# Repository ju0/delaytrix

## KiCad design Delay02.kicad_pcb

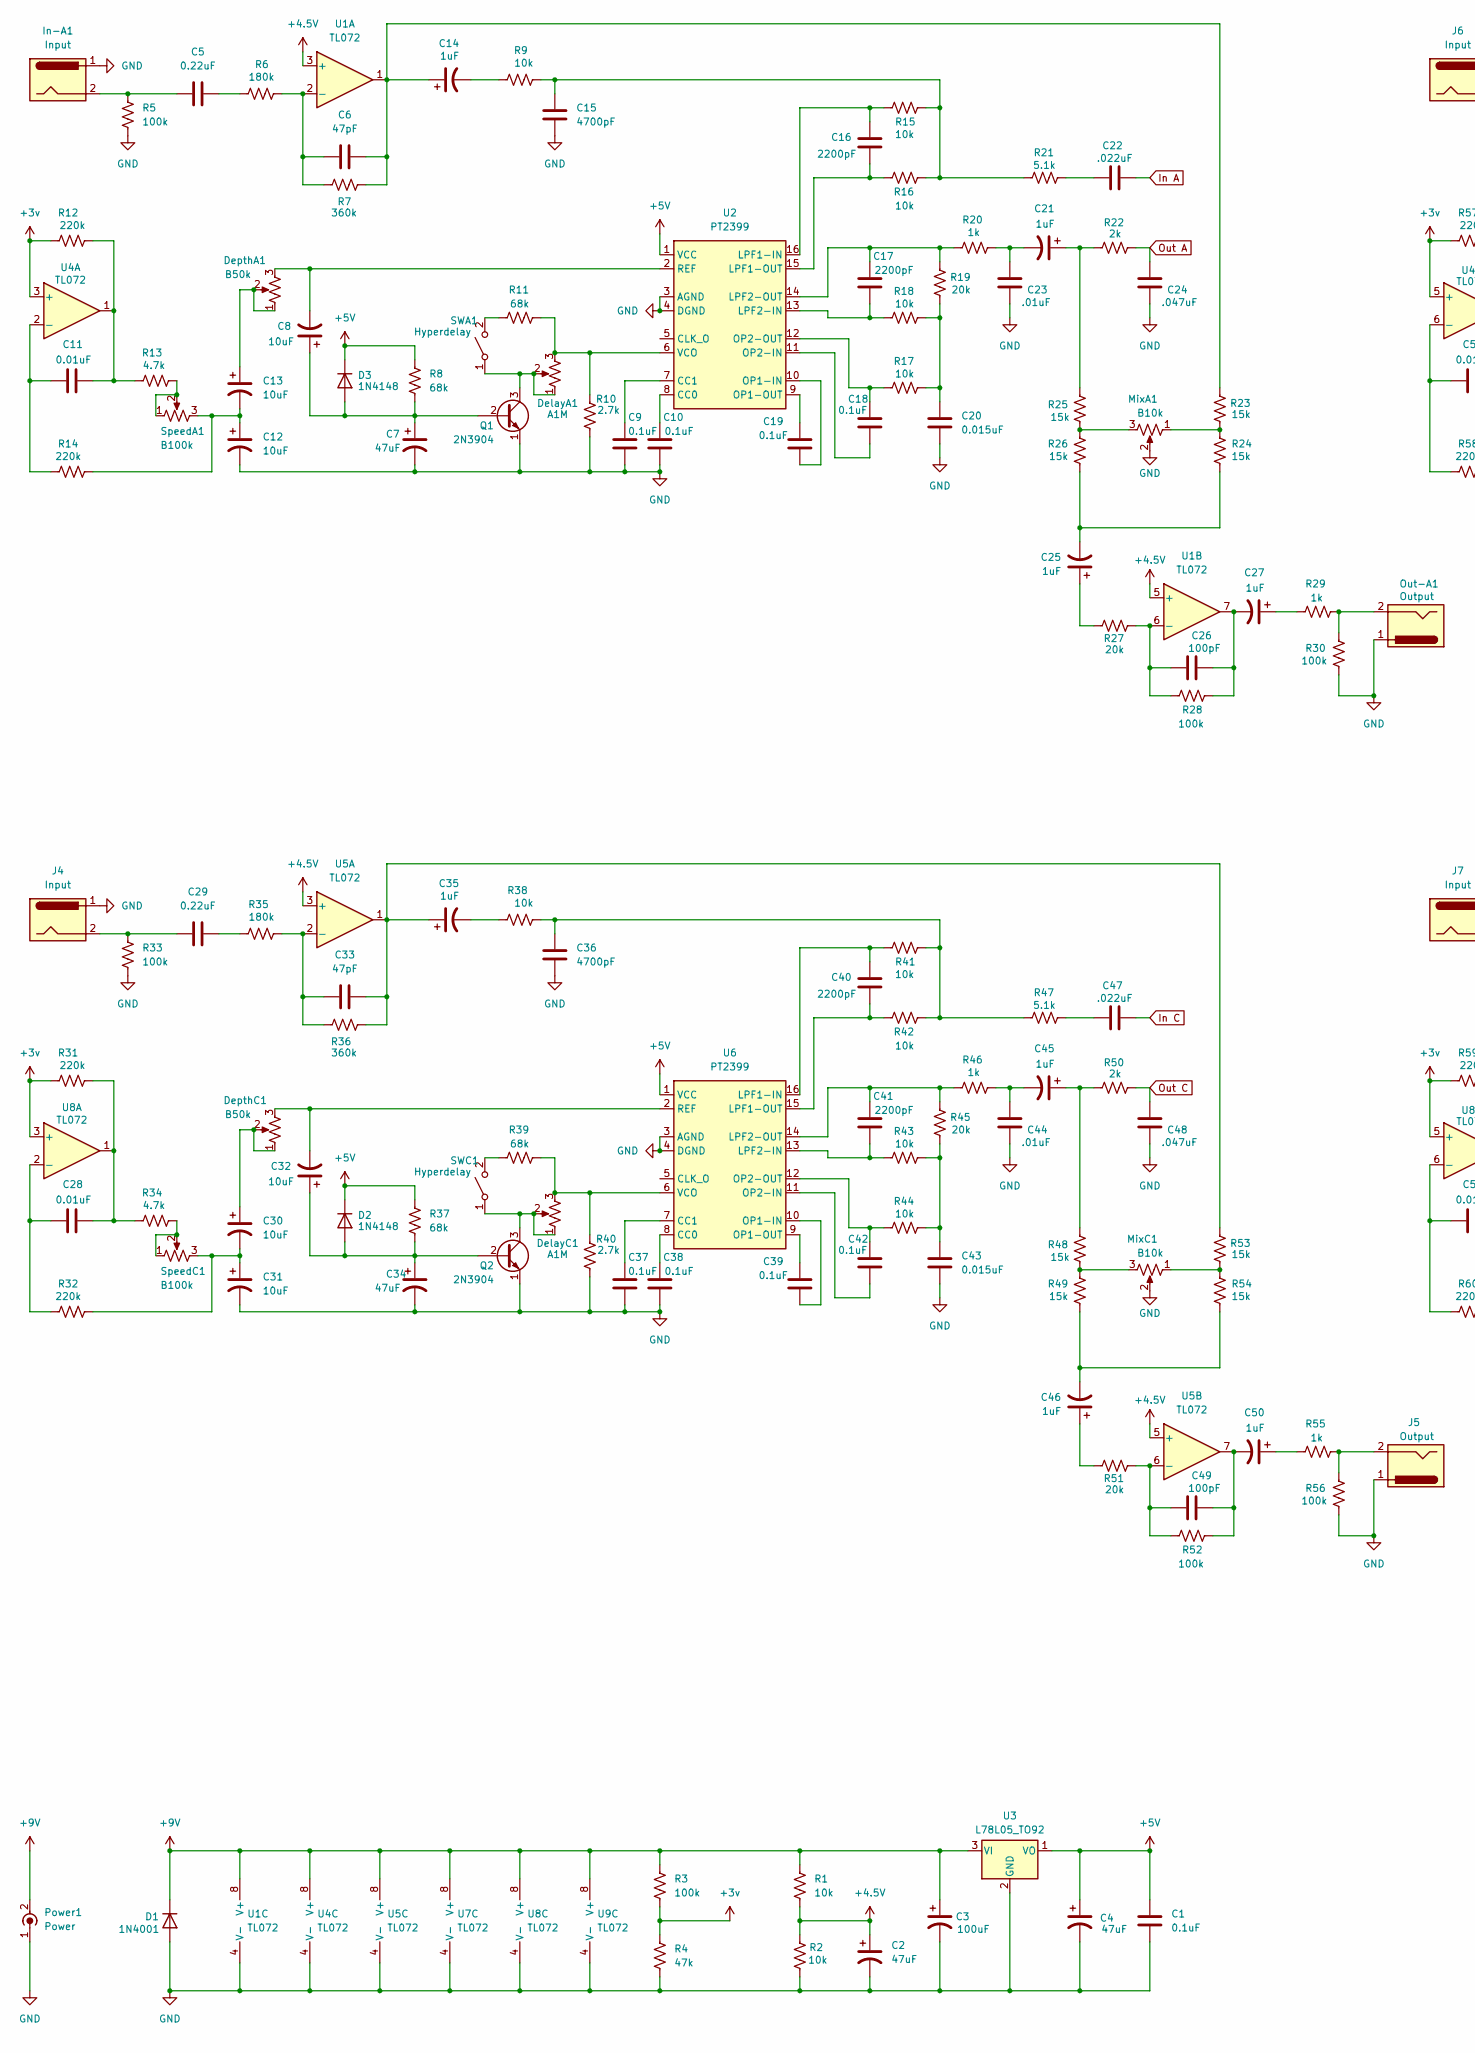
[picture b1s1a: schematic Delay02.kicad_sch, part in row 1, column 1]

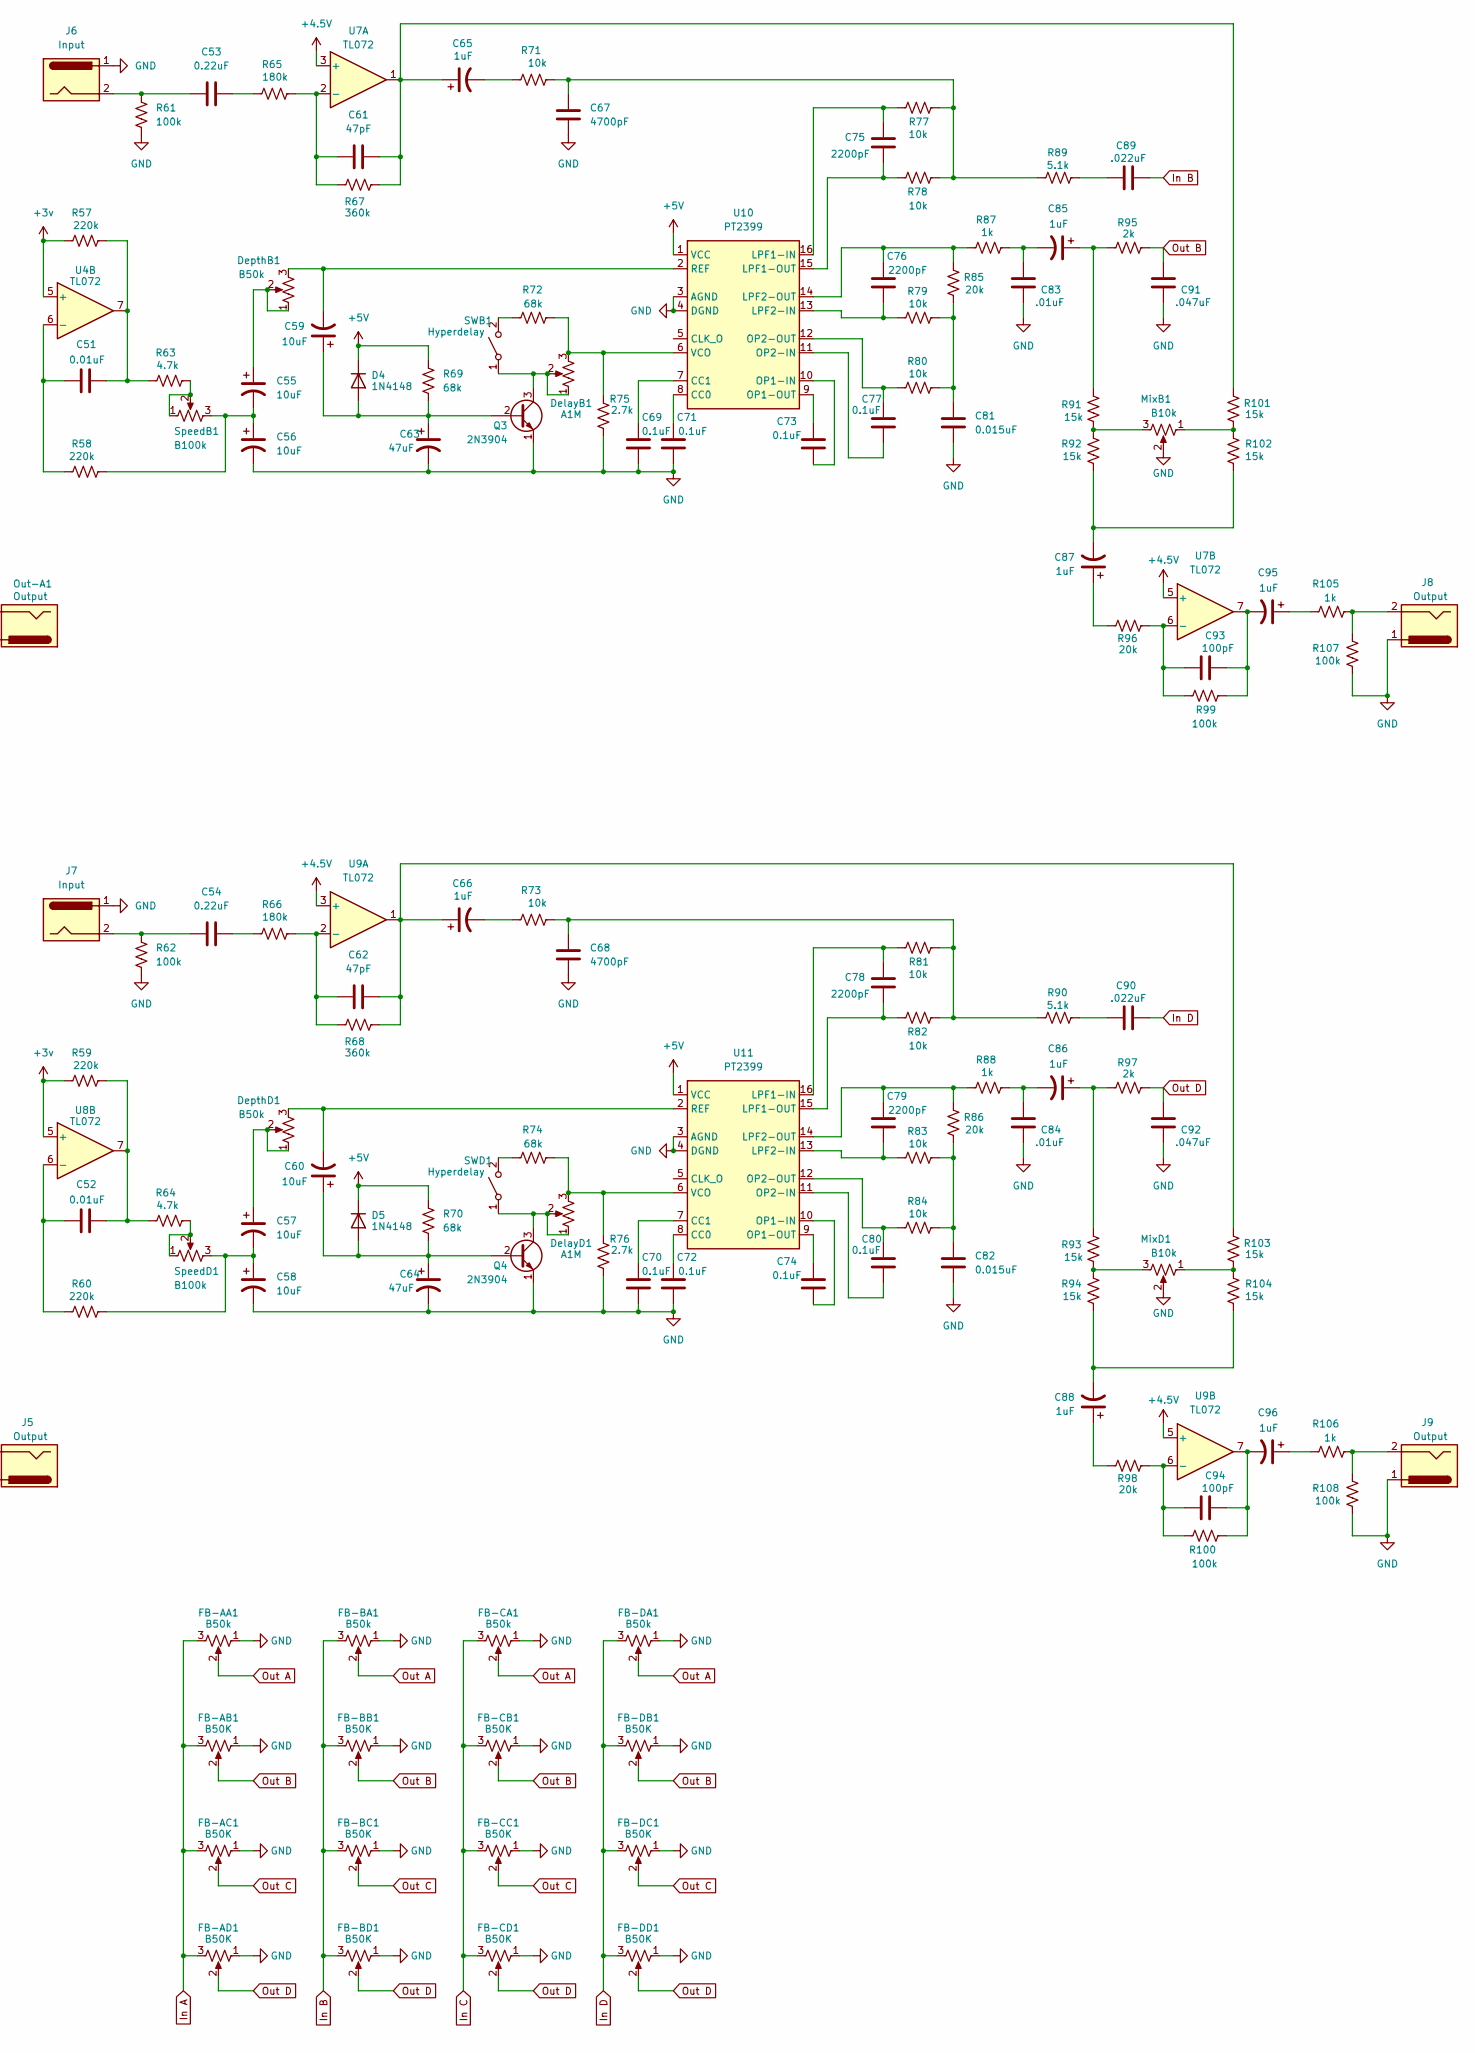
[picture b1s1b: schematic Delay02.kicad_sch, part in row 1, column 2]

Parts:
C1, C9, C10, C18, C19, C37, C38, C39, C42, C69, C70, C71, C72, C73, C74, C77, C80: 0.1uF; C_Disc_D3.0mm_W1.6mm_P2.50mm
C2, C4, C7, C34, C63, C64: 47uF; CP_Radial_D4.0mm_P1.50mm
C3: 100uF; CP_Radial_D4.0mm_P1.50mm
C5, C29, C53, C54: 0.22uF; C_Disc_D3.0mm_W1.6mm_P2.50mm
C6, C33, C61, C62: 47pF; C_Disc_D3.0mm_W1.6mm_P2.50mm
C8, C12, C13, C30, C31, C32, C55, C56, C57, C58, C59, C60: 10uF; CP_Radial_D4.0mm_P1.50mm
C11, C28, C51, C52: 0.01uF; C_Disc_D3.0mm_W1.6mm_P2.50mm
C14, C21, C25, C27, C35, C45, C46, C50, C65, C66, C85, C86, C87, C88, C95, C96: 1uF; CP_Radial_D4.0mm_P1.50mm
C15, C36, C67, C68: 4700pF; C_Disc_D3.0mm_W1.6mm_P2.50mm
C16, C17, C40, C41, C75, C76, C78, C79: 2200pF; C_Disc_D3.0mm_W1.6mm_P2.50mm
C20, C43, C81, C82: 0.015uF; C_Disc_D3.0mm_W1.6mm_P2.50mm
C22, C47, C89, C90: .022uF; C_Disc_D3.0mm_W1.6mm_P2.50mm
C23, C44, C83, C84: .01uF; C_Disc_D3.0mm_W1.6mm_P2.50mm
C24, C48, C91, C92: .047uF; C_Disc_D3.0mm_W1.6mm_P2.50mm
C26, C49, C93, C94: 100pF; C_Disc_D3.0mm_W1.6mm_P2.50mm
D1: 1N4001; D_DO-41_SOD81_P10.16mm_Horizontal
D2, D3, D4, D5: 1N4148; D_DO-35_SOD27_P7.62mm_Horizontal
DelayA1: A1M; Potentiometer_Omeg_PC16BU_Vertical_JU
DelayB1: A1M; Potentiometer_Omeg_PC16BU_Vertical_JU
DelayC1: A1M; Potentiometer_Omeg_PC16BU_Vertical_JU
DelayD1: A1M; Potentiometer_Omeg_PC16BU_Vertical_JU
DepthA1: B50k; Potentiometer_Omeg_PC16BU_Vertical_JU
DepthB1: B50k; Potentiometer_Omeg_PC16BU_Vertical_JU
DepthC1: B50k; Potentiometer_Omeg_PC16BU_Vertical_JU
DepthD1: B50k; Potentiometer_Omeg_PC16BU_Vertical_JU
FB-AA1: B50k; Potentiometer_Omeg_PC16BU_Vertical_JU
FB-AB1: B50K; Potentiometer_Omeg_PC16BU_Vertical_JU
FB-AC1: B50K; Potentiometer_Omeg_PC16BU_Vertical_JU
FB-AD1: B50K; Potentiometer_Omeg_PC16BU_Vertical_JU
FB-BA1: B50k; Potentiometer_Omeg_PC16BU_Vertical_JU
FB-BB1: B50K; Potentiometer_Omeg_PC16BU_Vertical_JU
FB-BC1: B50K; Potentiometer_Omeg_PC16BU_Vertical_JU
FB-BD1: B50K; Potentiometer_Omeg_PC16BU_Vertical_JU
FB-CA1: B50k; Potentiometer_Omeg_PC16BU_Vertical_JU
FB-CB1: B50K; Potentiometer_Omeg_PC16BU_Vertical_JU
FB-CC1: B50K; Potentiometer_Omeg_PC16BU_Vertical_JU
FB-CD1: B50K; Potentiometer_Omeg_PC16BU_Vertical_JU
FB-DA1: B50k; Potentiometer_Omeg_PC16BU_Vertical_JU
FB-DB1: B50K; Potentiometer_Omeg_PC16BU_Vertical_JU
FB-DC1: B50K; Potentiometer_Omeg_PC16BU_Vertical_JU
FB-DD1: B50K; Potentiometer_Omeg_PC16BU_Vertical_JU
In-A1: Input; SolderWire-0.1sqmm_1x02_P3.6mm_D0.4mm_OD1mm
J4, J6, J7: Input; SolderWire-0.1sqmm_1x02_P3.6mm_D0.4mm_OD1mm
J5, J8, J9: Output; SolderWire-0.1sqmm_1x02_P3.6mm_D0.4mm_OD1mm
MixA1: B10k; Potentiometer_Omeg_PC16BU_Vertical_JU
MixB1: B10k; Potentiometer_Omeg_PC16BU_Vertical_JU
MixC1: B10k; Potentiometer_Omeg_PC16BU_Vertical_JU
MixD1: B10k; Potentiometer_Omeg_PC16BU_Vertical_JU
Out-A1: Output; SolderWire-0.1sqmm_1x02_P3.6mm_D0.4mm_OD1mm
Power1: Power; SolderWire-0.1sqmm_1x02_P3.6mm_D0.4mm_OD1mm
Q1, Q2, Q3, Q4: 2N3904; TO-92_Inline
R1, R2, R9, R15, R16, R17, R18, R38, R41, R42, R43, R44, R71, R73, R77, R78, R79, R80, R81, R82, R83, R84: 10k; R_Axial_DIN0204_L3.6mm_D1.6mm_P5.08mm_Horizontal-JU
R3, R5, R28, R30, R33, R52, R56, R61, R62, R99, R100, R107, R108: 100k; R_Axial_DIN0204_L3.6mm_D1.6mm_P5.08mm_Horizontal-JU
R4: 47k; R_Axial_DIN0204_L3.6mm_D1.6mm_P5.08mm_Horizontal-JU
R6, R35, R65, R66: 180k; R_Axial_DIN0204_L3.6mm_D1.6mm_P5.08mm_Horizontal-JU
R7, R36, R67, R68: 360k; R_Axial_DIN0204_L3.6mm_D1.6mm_P5.08mm_Horizontal-JU
R8, R11, R37, R39, R69, R70, R72, R74: 68k; R_Axial_DIN0204_L3.6mm_D1.6mm_P5.08mm_Horizontal-JU
R10, R40, R75, R76: 2.7k; R_Axial_DIN0204_L3.6mm_D1.6mm_P5.08mm_Horizontal-JU
R12, R14, R31, R32, R57, R58, R59, R60: 220k; R_Axial_DIN0204_L3.6mm_D1.6mm_P5.08mm_Horizontal-JU
R13, R34, R63, R64: 4.7k; R_Axial_DIN0204_L3.6mm_D1.6mm_P5.08mm_Horizontal-JU
R19, R27, R45, R51, R85, R86, R96, R98: 20k; R_Axial_DIN0204_L3.6mm_D1.6mm_P5.08mm_Horizontal-JU
R20, R29, R46, R55, R87, R88, R105, R106: 1k; R_Axial_DIN0204_L3.6mm_D1.6mm_P5.08mm_Horizontal-JU
R21, R47, R89, R90: 5.1k; R_Axial_DIN0204_L3.6mm_D1.6mm_P5.08mm_Horizontal-JU
R22, R50, R95, R97: 2k; R_Axial_DIN0204_L3.6mm_D1.6mm_P5.08mm_Horizontal-JU
R23, R24, R25, R26, R48, R49, R53, R54, R91, R92, R93, R94, R101, R102, R103, R104: 15k; R_Axial_DIN0204_L3.6mm_D1.6mm_P5.08mm_Horizontal-JU
SWA1: Hyperdelay; SolderWire-0.1sqmm_1x02_P3.6mm_D0.4mm_OD1mm
SWB1: Hyperdelay; SolderWire-0.1sqmm_1x02_P3.6mm_D0.4mm_OD1mm
SWC1: Hyperdelay; SolderWire-0.1sqmm_1x02_P3.6mm_D0.4mm_OD1mm
SWD1: Hyperdelay; SolderWire-0.1sqmm_1x02_P3.6mm_D0.4mm_OD1mm
SpeedA1: B100k; Potentiometer_Omeg_PC16BU_Vertical_JU
SpeedB1: B100k; Potentiometer_Omeg_PC16BU_Vertical_JU
SpeedC1: B100k; Potentiometer_Omeg_PC16BU_Vertical_JU
SpeedD1: B100k; Potentiometer_Omeg_PC16BU_Vertical_JU
U1, U4, U5, U7, U8, U9: TL072; DIP-8_W7.62mm_Socket_LongPads
U2, U6, U10, U11: PT2399; DIP-16_W7.62mm
U3: L78L05_TO92; TO-92_Inline

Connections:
+3v: R3.2, R4.1, R12.1, R31.1, R57.1, R59.1, U4.3 (+), U4.5 (+), U8.3 (+), U8.5 (+)
+4.5V: C2.1, R1.2, R2.2, U1.3 (+), U1.5 (+), U5.3 (+), U5.5 (+), U7.3 (+), U7.5 (+), U9.3 (+), U9.5 (+)
+5V: C1.2, C4.1, D2.1 (K), D3.1 (K), D4.1 (K), D5.1 (K), R8.1, R37.1, R69.1, R70.1, U2.1 (VCC), U3.1 (VO), U6.1 (VCC), U10.1 (VCC), U11.1 (VCC)
+9V: C3.1, D1.1 (K), Power1.2 (Ext), R1.1, R3.1, U1.8 (V+), U3.3 (VI), U4.8 (V+), U5.8 (V+), U7.8 (V+), U8.8 (V+), U9.8 (V+); also elsewhere on the board
GND: C1.1, C2.2, C3.2, C4.2, C7.2, C9.1, C10.1, C12.2, C15.2, C20.2, C23.1, C24.1, C31.2, C34.2, C36.2, C37.1, C38.1, C43.2, C44.1, C48.1, C56.2, C58.2, C63.2, C64.2, C67.2, C68.2, C69.1, C70.1, C71.1, C72.1, C81.2, C82.2, C83.1, C84.1, C91.1, C92.1, D1.2 (A), FB-AA1.1, FB-AB1.1, FB-AC1.1, FB-AD1.1, FB-BA1.1, FB-BB1.1, FB-BC1.1, FB-BD1.1, FB-CA1.1, FB-CB1.1, FB-CC1.1, FB-CD1.1, FB-DA1.1, FB-DB1.1, FB-DC1.1, FB-DD1.1, In-A1.1, J4.1, J5.1, J6.1, J7.1, J8.1, J9.1, MixA1.2, MixB1.2, MixC1.2, MixD1.2, Out-A1.1, Power1.1 (In), Q1.1 (E), Q2.1 (E), Q3.1 (E), Q4.1 (E), R2.1, R4.2, R5.2, R10.2, R30.1, R33.2, R40.2, R56.1, R61.2, R62.2, R75.2, R76.2, R107.1, R108.1, U1.4 (V-), U2.3 (AGND), U2.4 (DGND), U3.2 (GND), U4.4 (V-), U5.4 (V-), U6.3 (AGND), U6.4 (DGND), U7.4 (V-), U8.4 (V-), U9.4 (V-), U10.3 (AGND), U10.4 (DGND), U11.3 (AGND), U11.4 (DGND); also elsewhere on the board
In A: C22.1, FB-AA1.3, FB-AB1.3, FB-AC1.3, FB-AD1.3
In B: C89.1, FB-BA1.3, FB-BB1.3, FB-BC1.3, FB-BD1.3
In C: C47.1, FB-CA1.3, FB-CB1.3, FB-CC1.3, FB-CD1.3
In D: C90.1, FB-DA1.3, FB-DB1.3, FB-DC1.3, FB-DD1.3
unnamed: C5.1, R6.1
unnamed 10: C5.2, In-A1.2, R5.1; also elsewhere on the board
unnamed: C11.2, R12.2, R13.1, U4.1
unnamed: C12.1, C13.2, R14.2, SpeedA1.3
unnamed: C13.1, DepthA1.1, DepthA1.2
unnamed: C6.1, C14.1, R7.2, R23.1, U1.1
unnamed: C14.2, R9.1
unnamed: C15.1, R9.2, R15.2, R16.2, R21.1
unnamed: C20.1, R17.2, R18.2, R19.2
unnamed: C21.1, R22.1, R25.2
unnamed: C21.2, C23.2, R20.2
unnamed: C22.2, R21.2
unnamed: C25.1, R27.1
unnamed: C25.2, R24.2, R26.1
unnamed: C26.1, C27.2, R28.2, U1.7
unnamed: C27.1, R29.1
unnamed: C28.2, R31.2, R34.1, U8.1
unnamed: C29.1, R35.1
unnamed: C29.2, J4.2, R33.1
unnamed: C30.1, DepthC1.1, DepthC1.2
unnamed: C30.2, C31.1, R32.2, SpeedC1.3
unnamed: C33.1, C35.1, R36.2, R53.1, U5.1
unnamed: C35.2, R38.1
unnamed: C36.1, R38.2, R41.2, R42.2, R47.1
unnamed: C43.1, R43.2, R44.2, R45.2
unnamed: C44.2, C45.2, R46.2
unnamed: C45.1, R48.2, R50.1
unnamed: C46.1, R51.1
unnamed: C46.2, R49.1, R54.2
unnamed: C47.2, R47.2
unnamed: C49.1, C50.2, R52.2, U5.7
unnamed: C50.1, R55.1
unnamed: C51.2, R57.2, R63.1, U4.7
unnamed: C52.2, R59.2, R64.1, U8.7
unnamed: C53.1, R65.1
unnamed: C53.2, J6.2, R61.1
unnamed: C54.1, R66.1
unnamed: C54.2, J7.2, R62.1
unnamed: C55.1, DepthB1.1, DepthB1.2
unnamed: C55.2, C56.1, R58.2, SpeedB1.3
unnamed: C57.1, DepthD1.1, DepthD1.2
unnamed: C57.2, C58.1, R60.2, SpeedD1.3
unnamed: C61.1, C65.1, R67.2, R101.1, U7.1
unnamed: C62.1, C66.1, R68.2, R103.1, U9.1
unnamed: C65.2, R71.1
unnamed: C66.2, R73.1
unnamed: C67.1, R71.2, R77.2, R78.2, R89.1
unnamed: C68.1, R73.2, R81.2, R82.2, R90.1
unnamed: C81.1, R79.2, R80.2, R85.2
unnamed: C82.1, R83.2, R84.2, R86.2
unnamed: C83.2, C85.2, R87.2
unnamed: C84.2, C86.2, R88.2
unnamed: C85.1, R91.2, R95.1
unnamed: C86.1, R93.2, R97.1
unnamed: C87.1, R96.1
unnamed: C87.2, R92.1, R102.2
unnamed: C88.1, R98.1
unnamed: C88.2, R94.1, R104.2
unnamed: C89.2, R89.2
unnamed: C90.2, R90.2
unnamed: C93.1, C95.2, R99.2, U7.7
unnamed: C94.1, C96.2, R100.2, U9.7
unnamed: C95.1, R105.1
unnamed: C96.1, R106.1
unnamed: C32.1, C34.1, D2.2 (A), Q2.2 (B), R37.2
unnamed: C7.1, C8.1, D3.2 (A), Q1.2 (B), R8.2
unnamed: C59.1, C63.1, D4.2 (A), Q3.2 (B), R69.2
unnamed: C60.1, C64.1, D5.2 (A), Q4.2 (B), R70.2
unnamed: J5.2, R55.2, R56.2
unnamed: J8.2, R105.2, R107.2
unnamed: J9.2, R106.2, R108.2
unnamed: MixA1.1, R23.2, R24.1
unnamed: MixA1.3, R25.1, R26.2
unnamed: MixB1.1, R101.2, R102.1
unnamed: MixB1.3, R91.1, R92.2
unnamed: MixC1.1, R53.2, R54.1
unnamed: MixC1.3, R48.1, R49.2
unnamed: MixD1.1, R103.2, R104.1
unnamed: MixD1.3, R93.1, R94.2
unnamed 88: Out-A1.2, R29.2, R30.2; also elsewhere on the board
unnamed: DelayA1.1, DelayA1.2, Q1.3 (C), SWA1.1 (A)
unnamed: DelayC1.1, DelayC1.2, Q2.3 (C), SWC1.1 (A)
unnamed: DelayB1.1, DelayB1.2, Q3.3 (C), SWB1.1 (A)
unnamed: DelayD1.1, DelayD1.2, Q4.3 (C), SWD1.1 (A)
unnamed: R13.2, SpeedA1.1, SpeedA1.2
unnamed: R34.2, SpeedC1.1, SpeedC1.2
unnamed: R63.2, SpeedB1.1, SpeedB1.2
unnamed: R64.2, SpeedD1.1, SpeedD1.2
unnamed: R11.1, SWA1.2 (B)
unnamed: R72.1, SWB1.2 (B)
unnamed: R39.1, SWC1.2 (B)
unnamed: R74.1, SWD1.2 (B)
unnamed: C6.2, R6.2, R7.1, U1.2 (-)
unnamed: C26.2, R27.2, R28.1, U1.6 (-)
unnamed: C10.2, U2.8 (CC0)
unnamed: C9.2, U2.7 (CC1)
unnamed: C16.2, R15.1, U2.16 (LPF1-IN)
unnamed: C16.1, R16.1, U2.15 (LPF1-OUT)
unnamed: C17.2, R18.1, U2.13 (LPF2-IN)
unnamed: C17.1, R19.1, R20.1, U2.14 (LPF2-OUT)
unnamed: C19.1, U2.10 (OP1-IN)
unnamed: C19.2, U2.9 (OP1-OUT)
unnamed: C18.2, U2.11 (OP2-IN)
unnamed: C18.1, R17.1, U2.12 (OP2-OUT)
unnamed: C8.2, DepthA1.3, U2.2 (REF)
unnamed: DelayA1.3, R10.1, R11.2, U2.6 (VCO)
unnamed: C11.1, R14.1, U4.2 (-)
unnamed: C51.1, R58.1, U4.6 (-)
unnamed: C33.2, R35.2, R36.1, U5.2 (-)
unnamed: C49.2, R51.2, R52.1, U5.6 (-)
unnamed: C38.2, U6.8 (CC0)
unnamed: C37.2, U6.7 (CC1)
unnamed: C40.2, R41.1, U6.16 (LPF1-IN)
unnamed: C40.1, R42.1, U6.15 (LPF1-OUT)
unnamed: C41.2, R43.1, U6.13 (LPF2-IN)
unnamed: C41.1, R45.1, R46.1, U6.14 (LPF2-OUT)
unnamed: C39.1, U6.10 (OP1-IN)
unnamed: C39.2, U6.9 (OP1-OUT)
unnamed: C42.2, U6.11 (OP2-IN)
unnamed: C42.1, R44.1, U6.12 (OP2-OUT)
unnamed: C32.2, DepthC1.3, U6.2 (REF)
unnamed: DelayC1.3, R39.2, R40.1, U6.6 (VCO)
unnamed: C61.2, R65.2, R67.1, U7.2 (-)
unnamed: C93.2, R96.2, R99.1, U7.6 (-)
unnamed: C28.1, R32.1, U8.2 (-)
unnamed: C52.1, R60.1, U8.6 (-)
unnamed: C62.2, R66.2, R68.1, U9.2 (-)
unnamed: C94.2, R98.2, R100.1, U9.6 (-)
unnamed: C71.2, U10.8 (CC0)
unnamed: C69.2, U10.7 (CC1)
unnamed: C75.2, R77.1, U10.16 (LPF1-IN)
unnamed: C75.1, R78.1, U10.15 (LPF1-OUT)
unnamed: C76.2, R79.1, U10.13 (LPF2-IN)
unnamed: C76.1, R85.1, R87.1, U10.14 (LPF2-OUT)
unnamed: C73.1, U10.10 (OP1-IN)
unnamed: C73.2, U10.9 (OP1-OUT)
unnamed: C77.2, U10.11 (OP2-IN)
unnamed: C77.1, R80.1, U10.12 (OP2-OUT)
unnamed: C59.2, DepthB1.3, U10.2 (REF)
unnamed: DelayB1.3, R72.2, R75.1, U10.6 (VCO)
unnamed: C72.2, U11.8 (CC0)
unnamed: C70.2, U11.7 (CC1)
unnamed: C78.2, R81.1, U11.16 (LPF1-IN)
unnamed: C78.1, R82.1, U11.15 (LPF1-OUT)
unnamed: C79.2, R83.1, U11.13 (LPF2-IN)
unnamed: C79.1, R86.1, R88.1, U11.14 (LPF2-OUT)
unnamed: C74.1, U11.10 (OP1-IN)
unnamed: C74.2, U11.9 (OP1-OUT)
unnamed: C80.2, U11.11 (OP2-IN)
unnamed: C80.1, R84.1, U11.12 (OP2-OUT)
unnamed: C60.2, DepthD1.3, U11.2 (REF)
unnamed: DelayD1.3, R74.2, R76.1, U11.6 (VCO)
Out A: C24.2, FB-AA1.2, FB-BA1.2, FB-CA1.2, FB-DA1.2, R22.2
Out B: C91.2, FB-AB1.2, FB-BB1.2, FB-CB1.2, FB-DB1.2, R95.2
Out C: C48.2, FB-AC1.2, FB-BC1.2, FB-CC1.2, FB-DC1.2, R50.2
Out D: C92.2, FB-AD1.2, FB-BD1.2, FB-CD1.2, FB-DD1.2, R97.2

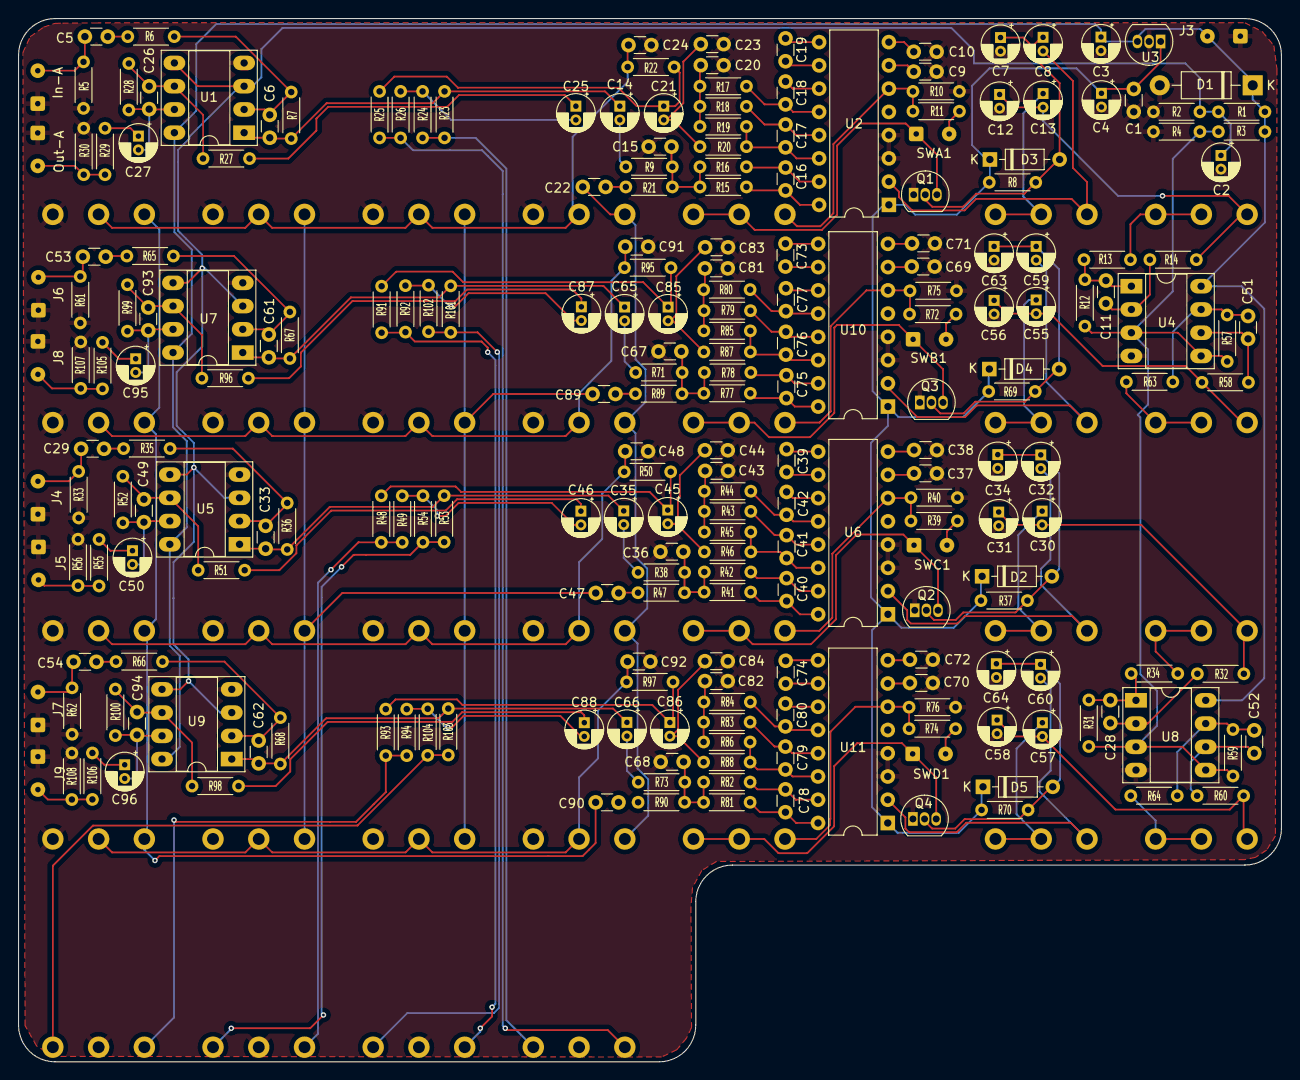
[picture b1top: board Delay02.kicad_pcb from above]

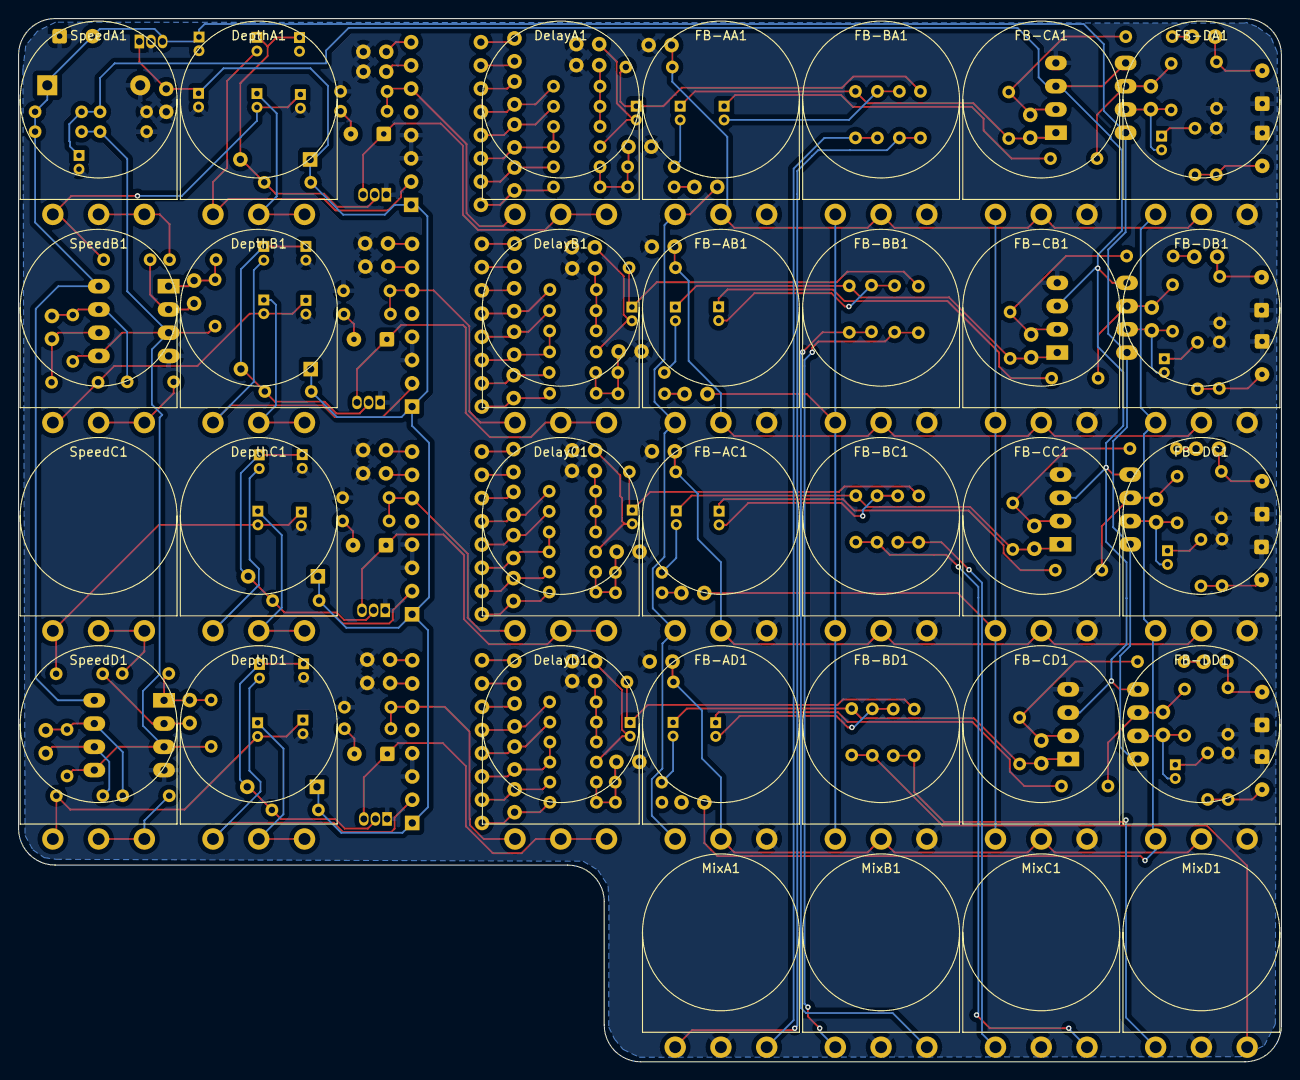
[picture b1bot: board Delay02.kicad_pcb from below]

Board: 2 copper layers, 138.0 x 114.0 mm, 269 parts (32 on the bottom side), 165 nets.

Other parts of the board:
In-A: Input; SolderWire-0.1sqmm_1x02_P3.6mm_D0.4mm_OD1mm
J3: Power; SolderWire-0.1sqmm_1x02_P3.6mm_D0.4mm_OD1mm
Out-A: Output; SolderWire-0.1sqmm_1x02_P3.6mm_D0.4mm_OD1mm

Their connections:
+9V: J3.2 (Ext); also elsewhere on the board
GND: In-A.1, J3.1 (In), Out-A.1; also elsewhere on the board
unnamed 10: In-A.2; also elsewhere on the board
unnamed 88: Out-A.2; also elsewhere on the board
